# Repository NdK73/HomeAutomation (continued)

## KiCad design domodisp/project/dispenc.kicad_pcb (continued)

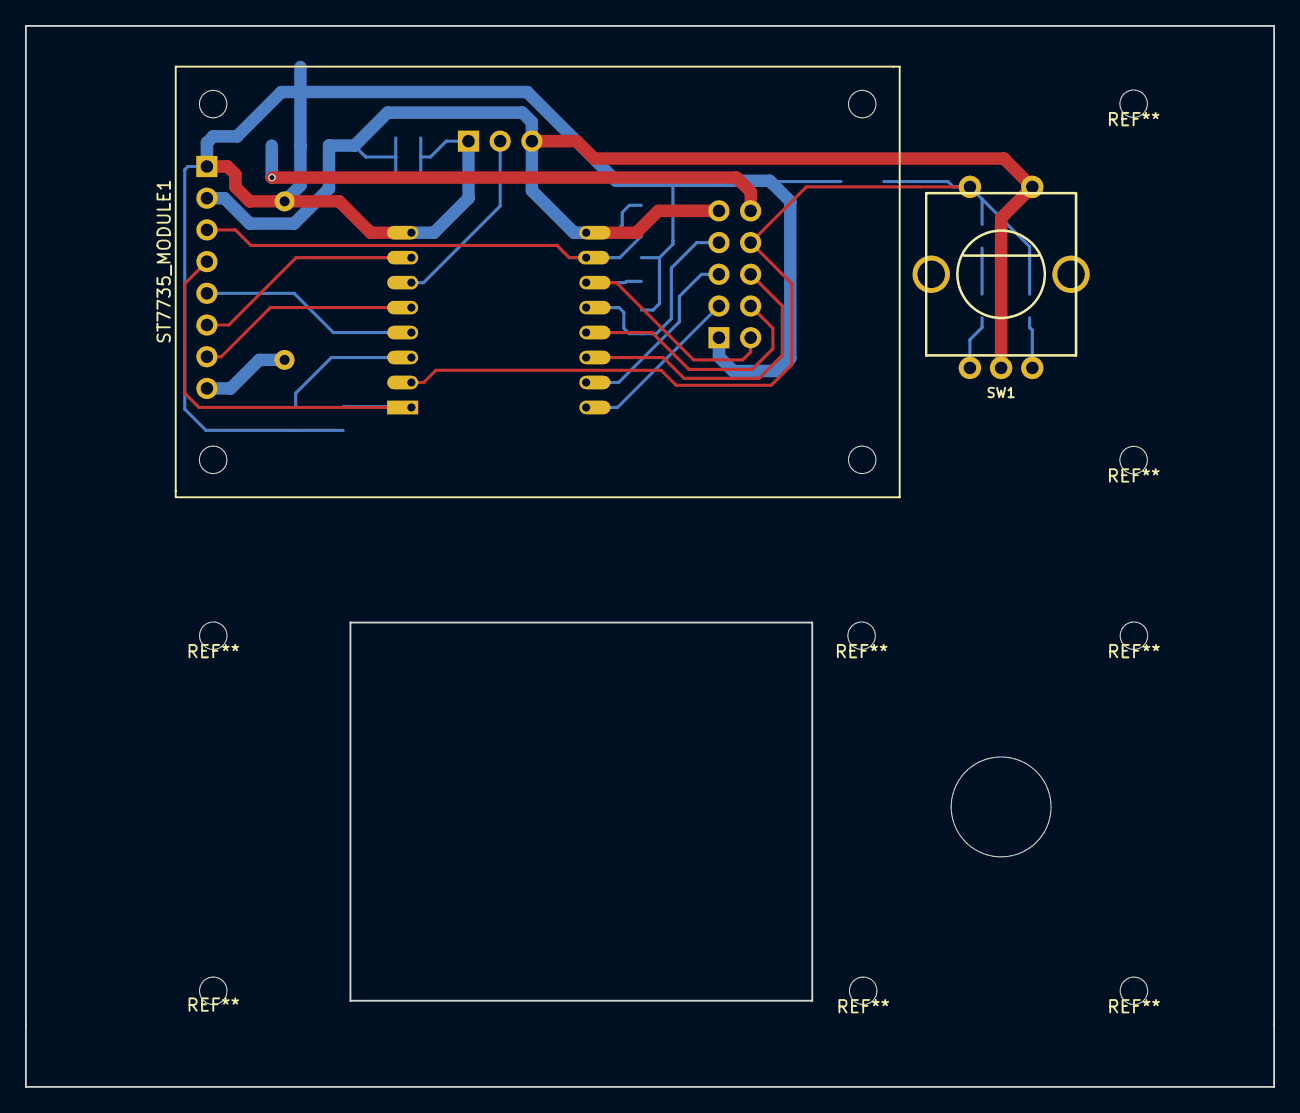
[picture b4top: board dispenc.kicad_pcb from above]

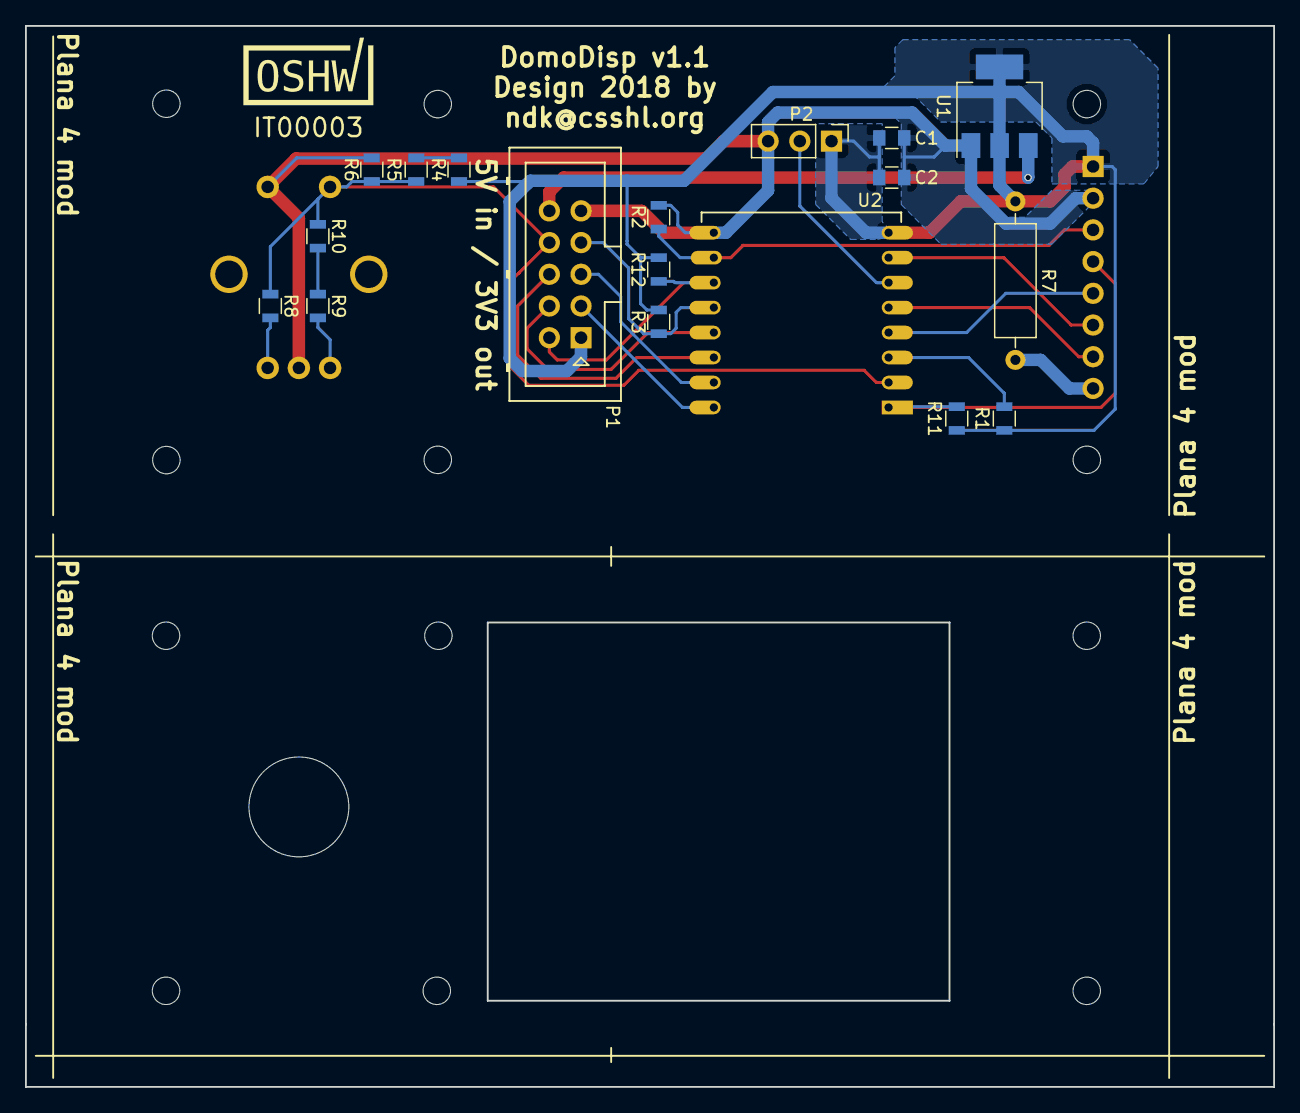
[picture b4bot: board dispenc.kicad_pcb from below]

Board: 2 copper layers, 100.0 x 85.0 mm, 21 parts (19 on the bottom side), 22 nets.

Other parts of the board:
OSHW_Mono_0.25_Scale: IT00003; OSHW_Mono_0.25_Scale
R12: 10k; R_0805

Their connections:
+3V3: R12.1; also elsewhere on the board
/DBG: R12.2; also elsewhere on the board

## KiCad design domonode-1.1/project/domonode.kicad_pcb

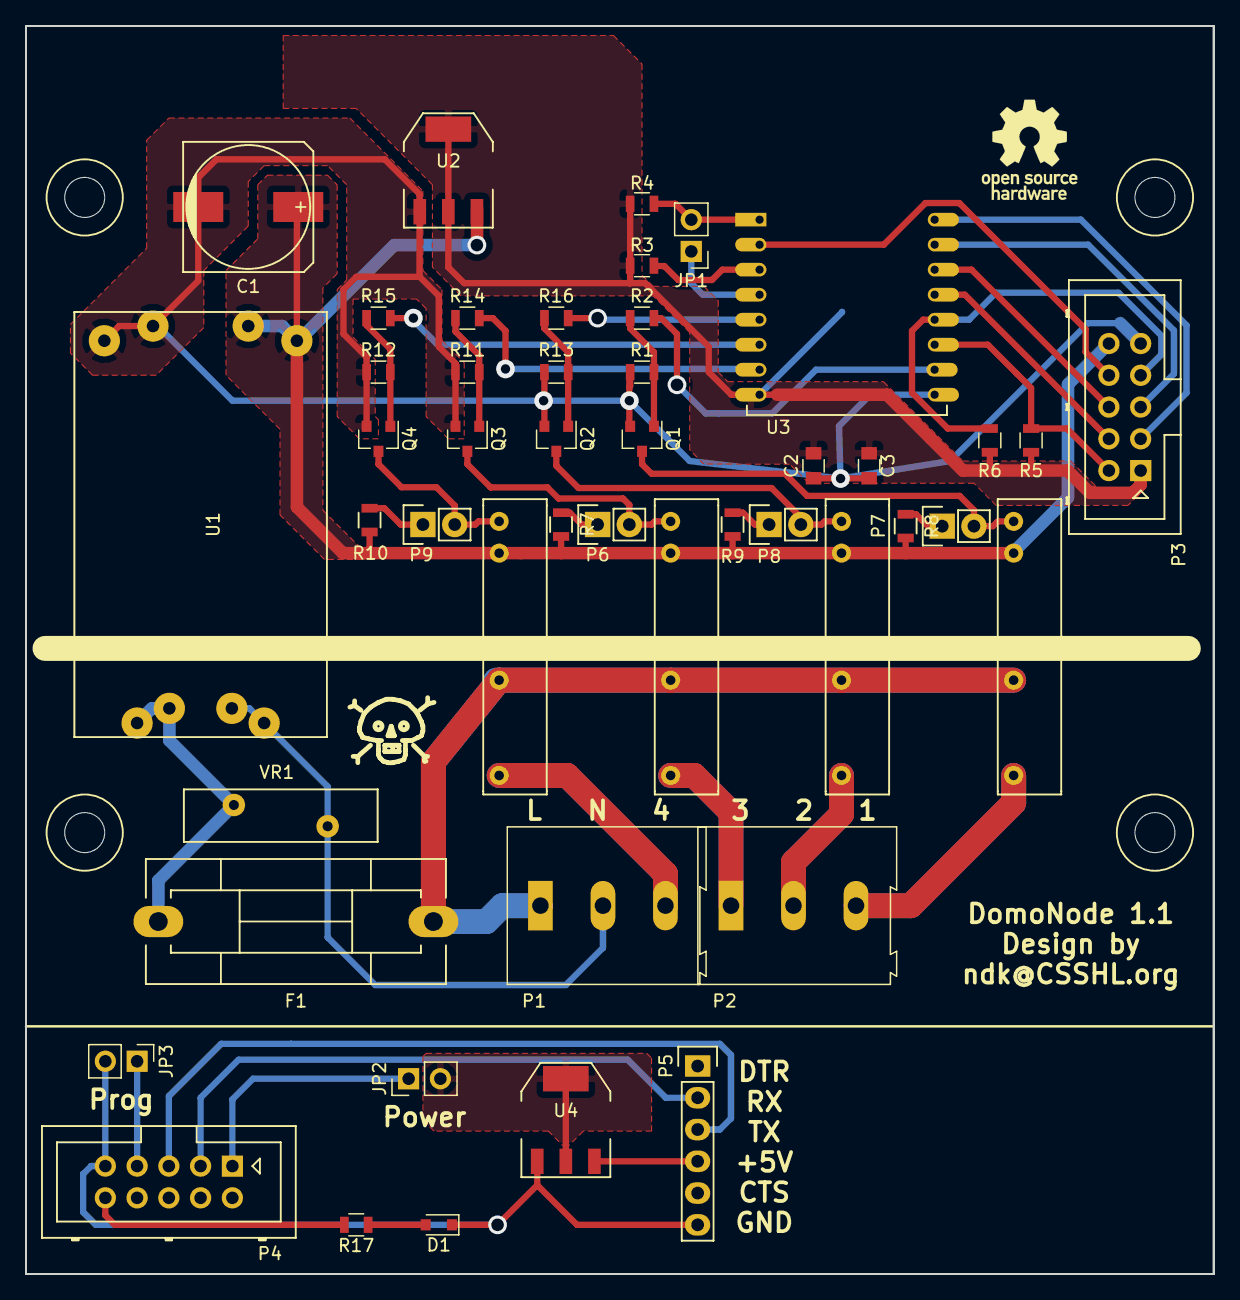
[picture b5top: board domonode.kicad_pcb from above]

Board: 2 copper layers, 95.0 x 99.8 mm, 48 parts (0 on the bottom side), 45 nets.

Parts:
BOX: Enclosure_DIN_6p_nomargin
C1: C; c_elec_10x10
C2: 10u; C_0805
C3: 100n; C_0805
D1: LED; D_0805
F1: FUSE; Fuseholder5x20_horiz_SemiClosed_Casing10x25mm
JP1: JUMPER; Pin_Header_Straight_1x02_Pitch2.54mm
JP2, JP3: Jumper; Pin_Header_Straight_1x02_Pitch2.54mm
P1, P2: CONN_01X03; AK300-3
P3, P4: CONN_2x5; Multicomp_MC9A12-1034_2x05x2.54mm_Straight
P5: CONN_01X06; Pin_Header_Straight_1x06
P6, P7, P8, P9: CONN_01X02; Pin_Header_Straight_1x02
Q1, Q2, Q3, Q4: 2n7002; SOT-23
R1, R3, R4, R5, R6, R11, R12, R13: 10k; R_0805
R2, R7, R8, R9, R10, R14, R15, R16, R17: 1k; R_0805
RL1, RL2, RL3, RL4: Omron_G3MB-202; G3MB
U1: HLK-PM01; ACDC-HLK+ND
U2, U4: AMS1117-3.3; SOT-223
U3: ESP-12
VR1: VR; RV_Disc_D15.5_W4.2_P7.5

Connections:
+3V3: C2.1, C3.1, P3.1, R3.1, R4.1, R5.1, R6.1, U2.2, U2.4, U3.8
+5V: C1.1, P3.10, R7.2, R8.2, R9.2, R10.2, RL1.3, RL2.3, RL3.3, RL4.3, U1.4, U2.3
/ADC: P3.8, U3.2
/DBG: P3.2, R5.2, U3.11
/L: F1.1, P1.1, RL1.2, RL2.2, RL3.2, RL4.2
/N: P1.2, U1.2, VR1.1
/PROG: P3.7, R6.2, U3.12
/P_GND: D1.1, JP3.2, P4.9, P5.6, U4.1
/P_PROG: JP3.1, P4.7
/P_RXD: P4.5, P5.3
/P_TXD: P4.3, P5.2
/RL1: R2.1, U3.10
/RL2: R16.1, U3.5
/RL3: R14.1, U3.7
/RL4: R15.1, U3.6
/RXD: P3.5, U3.15
/SCL: P3.4, U3.13
/SDA: P3.6, U3.14
/TXD: P3.3, U3.16
GND: C1.2, C2.2, C3.2, P3.9, Q1.2, Q2.2, Q3.2, Q4.2, R1.2, R11.2, R12.2, R13.2, U1.3, U2.1, U3.9
unnamed: D1.2, R17.1
unnamed: F1.2, U1.1, VR1.2
unnamed: JP1.1, U3.4
unnamed: JP1.2, R4.2, U3.1
unnamed: JP2.1, P4.1
unnamed: JP2.2, U4.2, U4.4
unnamed: P4.10, R17.2
unnamed: P5.4, U4.3
unnamed: P6.1, R7.1
unnamed: P6.2, Q3.3, RL3.4
unnamed: P7.1, R8.1
unnamed: P7.2, Q1.3, RL1.4
unnamed: P8.1, R9.1
unnamed: P8.2, Q2.3, RL2.4
unnamed: P9.1, R10.1
unnamed: P9.2, Q4.3, RL4.4
unnamed: Q1.1, R1.1, R2.2
unnamed: Q2.1, R13.1, R16.2
unnamed: Q3.1, R11.1, R14.2
unnamed: Q4.1, R12.1, R15.2
unnamed: R3.2, U3.3
RL1P: P2.3, RL1.1
RL2P: P2.2, RL2.1
RL3P: P2.1, RL3.1
RL4P: P1.3, RL4.1

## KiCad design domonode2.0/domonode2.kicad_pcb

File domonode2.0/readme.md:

## DomoNode 2.0

**Do not use:**. This folder is just for reference.

Evolution of DomoNode, but offers 6 inputs @ 230V, 6 SSR 2A@230V (each one have its own independent in and out lines, for maximum flexibility) and 8 independent LEDs, still in a 6-modules DIN rail enclosure. Kept SW compatibility with basic DomoNode (just the first 4 outputs), but different external connections.

Same expansion bus connector as the DomoNode 1.1.

I kept 2mm between L and N lines and it **ought** to be double-insulation, but it's actually not required: the user can't touch anything that is not already expected to be at 230V (screws in connectors) without opening the enclosure (the expansion connector **MUST NOT** be exposed).

The board requires two v-cuts around the central part, drawn on ECO2 layer (but not visible in the image). Once the two boards gets separated, the smaller one have to be mounted over the bigger one, using 2 **plastic** spacers (M3x15mm) and suitable 1x14 pins headers.

**Note**: Designed in KiCAD 5.1.5.

#### Known Problems

Fixed in v2.1:
 - **EPIC FAIL**: pulldowns instead of pullups on SDA and SCL :( -- it seems to work OK with internal ones, but could be a bit less stable
 - **FIXABLE FAIL**: SDA and SCL are reversed -- use Wire.begin(5,4);
 - Possible glitches at powerup on outputs: after a short power fail (~5s) MCP23017 outputs remain in the last state till setup() resets 'em (or indefinitely if you enter programming mode)
 - Trace for 3v3 to expansion connector is too thin
 - Traces from SSRs to Qn and from Qn to GND are too thin
 - Many traces are too long (to avoid vias)
 - You'll have to cut out about 2mm from the top of the break-out zone to allow the locks on the removable part of the connectors to engage

No need to fix in 2.1:
 - MCP23017 reset line goes to 3v3 instead of 5V

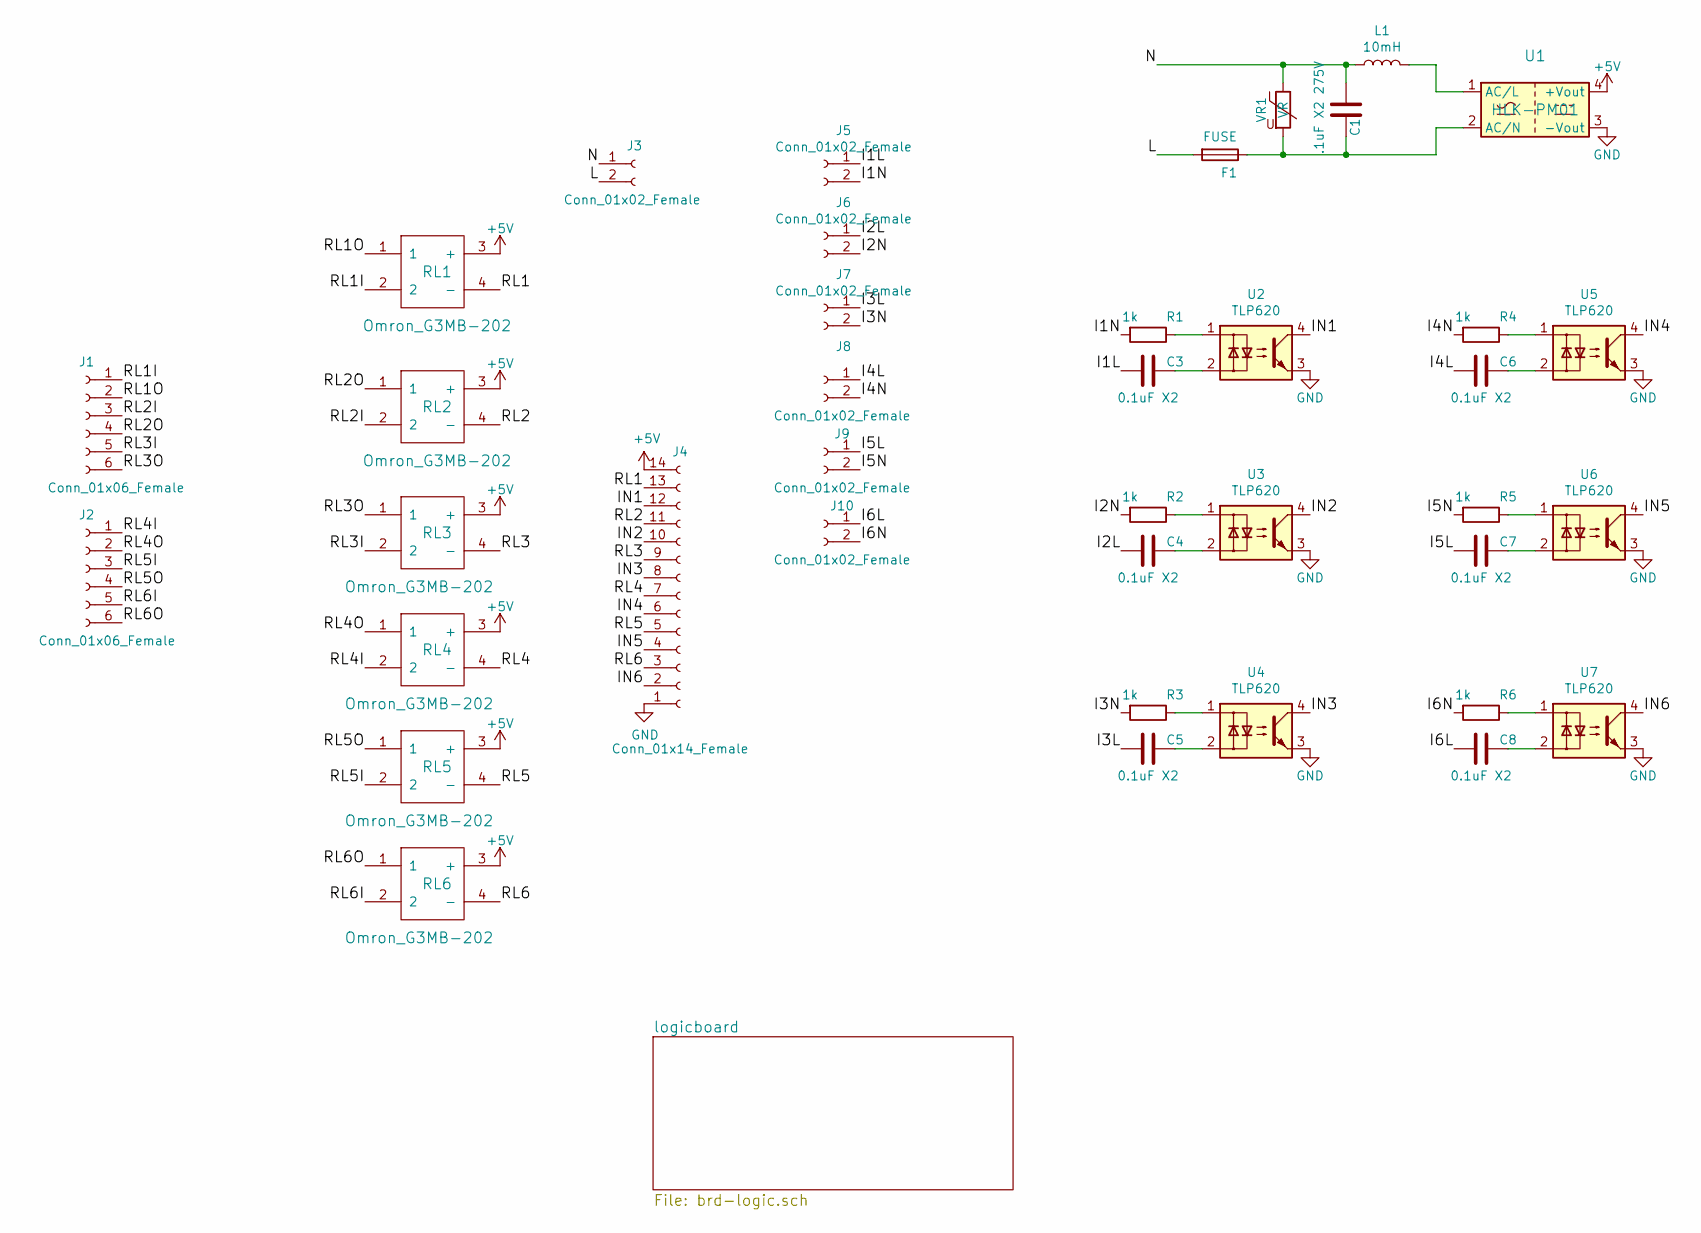
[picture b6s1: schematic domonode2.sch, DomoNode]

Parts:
C1: .1uF X2 275V; C_Rect_L13.0mm_W6.0mm_P10.00mm_FKS3_FKP3_MKS4
C3, C4, C5, C6, C7, C8: 0.1uF X2; C_Rect_L13.0mm_W6.0mm_P10.00mm_FKS3_FKP3_MKS4
F1: FUSE; Fuseholder5x20_horiz_SemiClosed_Casing10x25mm
J1, J2: Conn_01x06_Female; KF2EDGK-5.08-6
J3: Conn_01x02_Female; KF2EDGK-5.08-2
J4: Conn_01x14_Female; PinSocket_1x14_P2.54mm_Vertical
J5, J6, J7, J8, J9, J10: Conn_01x02_Female; KF2EDGK-3.81-2
L1: 10mH; INDUCTOR_0810
R1, R2, R3, R4, R5, R6: 1k; R_Axial_DIN0411_L9.9mm_D3.6mm_P12.70mm_Horizontal
RL1, RL2, RL3, RL4, RL5, RL6: Omron_G3MB-202; G3MB
U1: HLK-PM01; ACDC-HLK+ND
U2, U3, U4, U5, U6, U7: TLP620; DIP-4_W7.62mm_e_SOT-4
VR1: VR; RV_Disc_D15.5mm_W4.2mm_P7.5mm

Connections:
+5V: J4.14, RL1.3 (+), RL2.3 (+), RL3.3 (+), RL4.3 (+), RL5.3 (+), RL6.3 (+), U1.4 (+Vout)
/I1L: C3.2, J5.1
/I1N: J5.2, R1.2
/I2L: C4.2, J6.1
/I2N: J6.2, R2.2
/I3L: C5.2, J7.1
/I3N: J7.2, R3.2
/I4L: C6.2, J8.1
/I4N: J8.2, R4.2
/I5L: C7.2, J9.1
/I5N: J9.2, R5.2
/I6L: C8.2, J10.1
/I6N: J10.2, R6.2
/IN1: J4.12, U2.4
/IN2: J4.10, U3.4
/IN3: J4.8, U4.4
/IN4: J4.6, U5.4
/IN5: J4.4, U6.4
/IN6: J4.2, U7.4
/L: F1.2, J3.2
/N: C1.1, J3.1, L1.1, VR1.1
/RL1: J4.13, RL1.4 (-)
/RL1I: J1.1, RL1.2
/RL1O: J1.2, RL1.1
/RL2: J4.11, RL2.4 (-)
/RL2I: J1.3, RL2.2
/RL2O: J1.4, RL2.1
/RL3: J4.9, RL3.4 (-)
/RL3I: J1.5, RL3.2
/RL3O: J1.6, RL3.1
/RL4: J4.7, RL4.4 (-)
/RL4I: J2.1, RL4.2
/RL4O: J2.2, RL4.1
/RL5: J4.5, RL5.4 (-)
/RL5I: J2.3, RL5.2
/RL5O: J2.4, RL5.1
/RL6: J4.3, RL6.4 (-)
/RL6I: J2.5, RL6.2
/RL6O: J2.6, RL6.1
GND: J4.1, U1.3 (-Vout), U2.3, U3.3, U4.3, U5.3, U6.3, U7.3
unnamed: C1.2, F1.1, U1.2 (AC/N), VR1.2
unnamed: C3.1, U2.2
unnamed: C4.1, U3.2
unnamed: C5.1, U4.2
unnamed: C6.1, U5.2
unnamed: C7.1, U6.2
unnamed: C8.1, U7.2
unnamed: L1.2, U1.1 (AC/L)
unnamed: R1.1, U2.1
unnamed: R2.1, U3.1
unnamed: R3.1, U4.1
unnamed: R4.1, U5.1
unnamed: R5.1, U6.1
unnamed: R6.1, U7.1

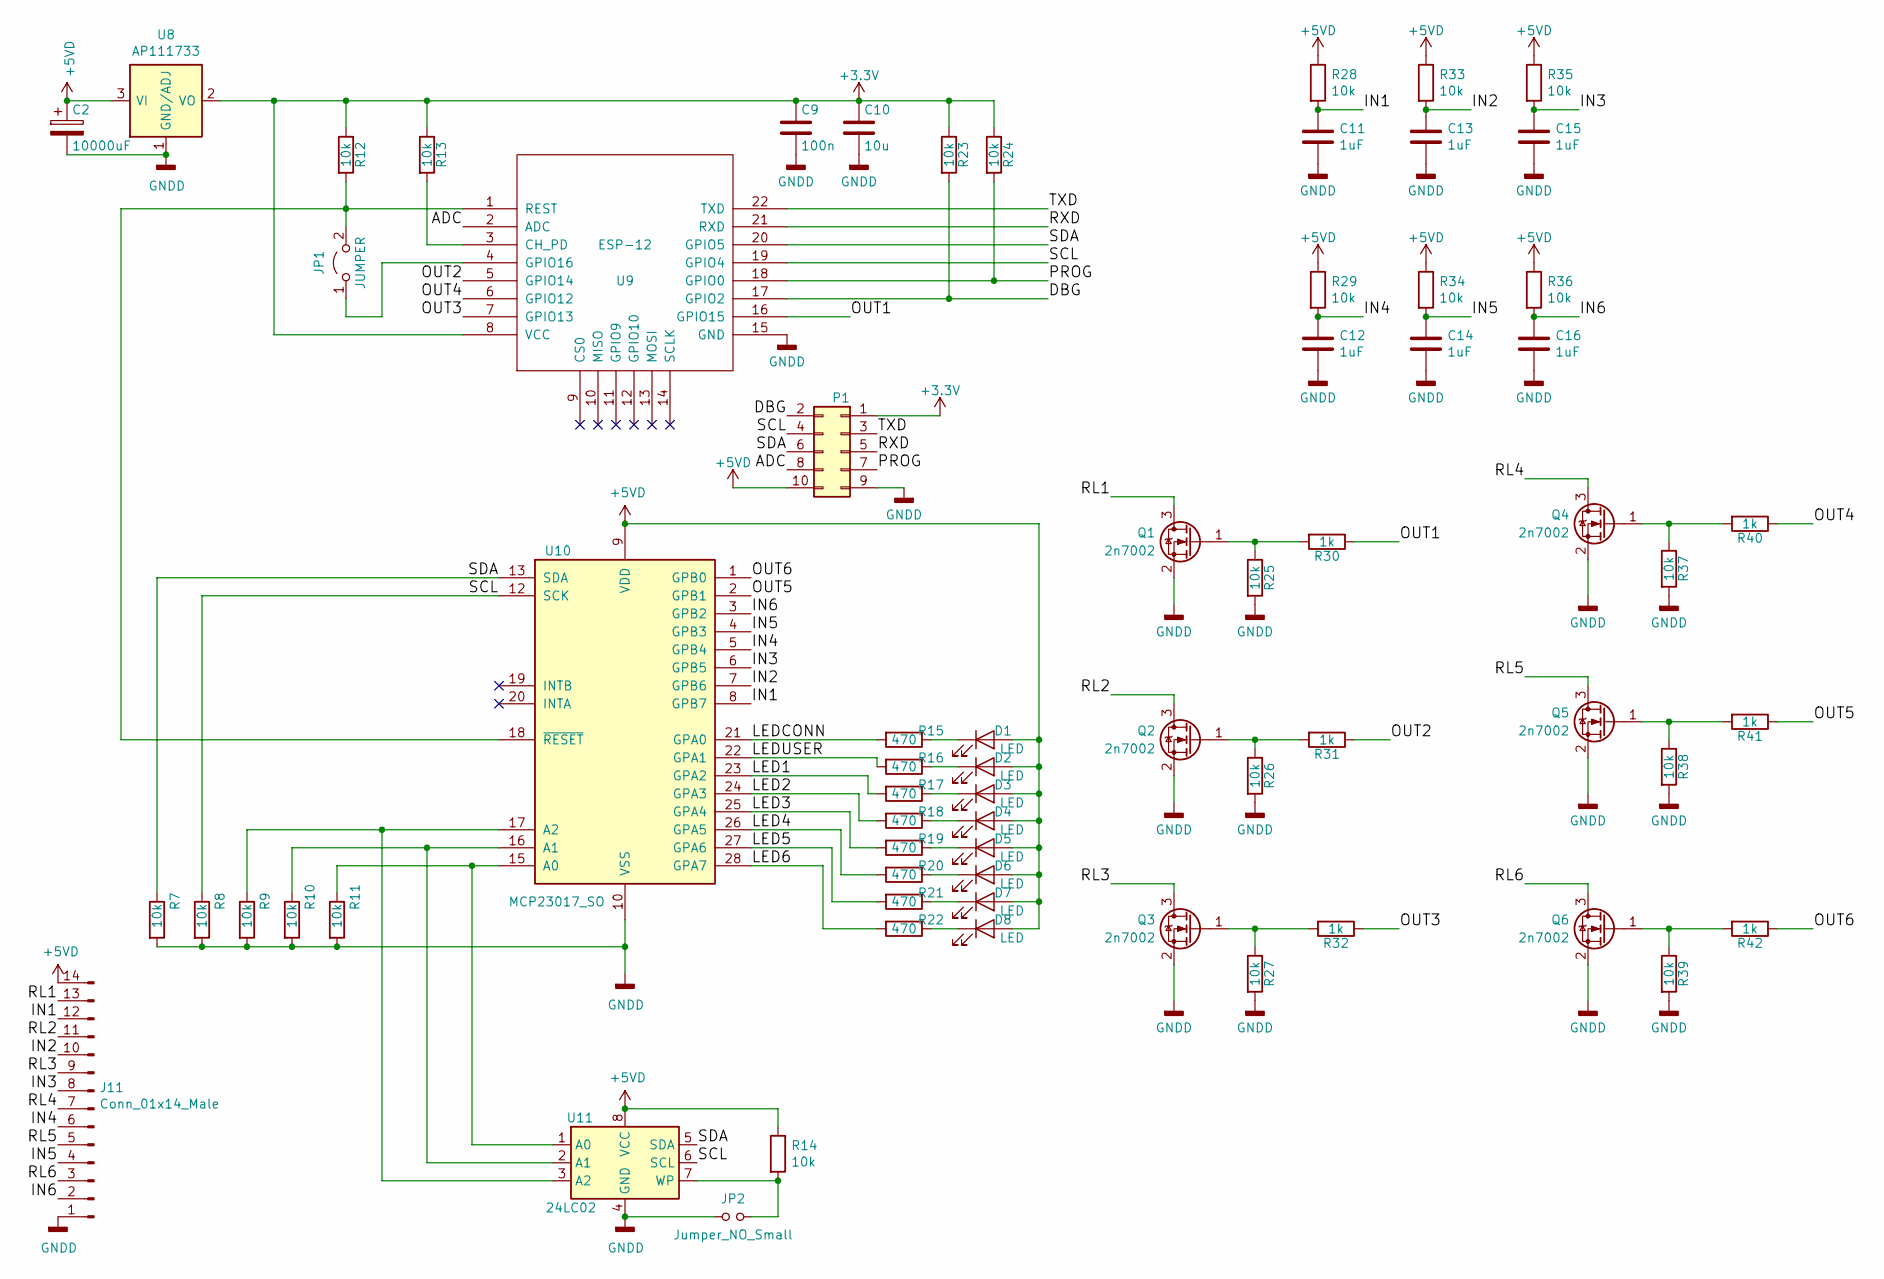
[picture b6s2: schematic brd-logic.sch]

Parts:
C2: 10000uF; CP_Elec_10x10
C9: 100n; C_0805_2012Metric
C10: 10u; C_0805_2012Metric
C11, C12, C13, C14, C15, C16: 1uF; C_0805_2012Metric
D1, D2, D3, D4, D5, D6, D7, D8: LED; LED_D3.0mm
J11: Conn_01x14_Male; PinSocket_1x14_P2.54mm_Vertical
JP1: JUMPER; PinSocket_1x02_P2.54mm_Vertical
JP2: Jumper_NO_Small; PinSocket_1x02_P2.54mm_Vertical
P1: CONN_2x5; Multicomp_MC9A12-1034_2x05_P2.54mm_Vertical
Q1, Q2, Q3, Q4, Q5, Q6: 2n7002; SOT-23
R7, R8, R9, R10, R11, R12, R13, R14, R23, R24, R25, R26, R27, R28, R29, R33, R34, R35, R36, R37, R38, R39: 10k; R_0805_2012Metric
R15, R16, R17, R18, R19, R20, R21, R22: 470; R_0805_2012Metric
R30, R31, R32, R40, R41, R42: 1k; R_0805_2012Metric
U8: AP111733; SOT-223-3_TabPin2
U9: ESP-12; ESP-12E
U10: MCP23017_SO; SOIC-28W_7.5x17.9mm_P1.27mm
U11: 24LC02; SOIC-8_3.9x4.9mm_P1.27mm

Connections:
+3V3: C9.1, C10.1, P1.1, R12.1, R13.1, R23.1, R24.1, U8.2 (VO), U9.8 (VCC)
+5VD: C2.1, D1.2 (A), D2.2 (A), D3.2 (A), D4.2 (A), D5.2 (A), D6.2 (A), D7.2 (A), D8.2 (A), J11.14, P1.10, R14.1, R28.1, R29.1, R33.1, R34.1, R35.1, R36.1, U8.3 (VI), U10.9 (VDD), U11.8 (VCC)
/logicboard/ADC: P1.8, U9.2 (ADC)
/logicboard/DBG: P1.2, R23.2, U9.17 (GPIO2)
/logicboard/IN1: C11.1, J11.12, R28.2, U10.8 (GPB7)
/logicboard/IN2: C13.1, J11.10, R33.2, U10.7 (GPB6)
/logicboard/IN3: C15.1, J11.8, R35.2, U10.6 (GPB5)
/logicboard/IN4: C12.1, J11.6, R29.2, U10.5 (GPB4)
/logicboard/IN5: C14.1, J11.4, R34.2, U10.4 (GPB3)
/logicboard/IN6: C16.1, J11.2, R36.2, U10.3 (GPB2)
/logicboard/LED1: R17.2, U10.23 (GPA2)
/logicboard/LED2: R18.2, U10.24 (GPA3)
/logicboard/LED3: R19.2, U10.25 (GPA4)
/logicboard/LED4: R20.2, U10.26 (GPA5)
/logicboard/LED5: R21.2, U10.27 (GPA6)
/logicboard/LED6: R22.2, U10.28 (GPA7)
/logicboard/LEDCONN: R15.2, U10.21 (GPA0)
/logicboard/LEDUSER: R16.2, U10.22 (GPA1)
/logicboard/OUT1: R30.1, U9.16 (GPIO15)
/logicboard/OUT2: R31.1, U9.5 (GPIO14)
/logicboard/OUT3: R32.1, U9.7 (GPIO13)
/logicboard/OUT4: R40.1, U9.6 (GPIO12)
/logicboard/OUT5: R41.1, U10.2 (GPB1)
/logicboard/OUT6: R42.1, U10.1 (GPB0)
/logicboard/PROG: P1.7, R24.2, U9.18 (GPIO0)
/logicboard/RL1: J11.13, Q1.3 (D)
/logicboard/RL2: J11.11, Q2.3 (D)
/logicboard/RL3: J11.9, Q3.3 (D)
/logicboard/RL4: J11.7, Q4.3 (D)
/logicboard/RL5: J11.5, Q5.3 (D)
/logicboard/RL6: J11.3, Q6.3 (D)
/logicboard/RXD: P1.5, U9.21 (RXD)
/logicboard/SCL: P1.4, R8.1, U9.19 (GPIO4), U10.12 (SCK), U11.6 (SCL)
/logicboard/SDA: P1.6, R7.1, U9.20 (GPIO5), U10.13 (SDA), U11.5 (SDA)
/logicboard/TXD: P1.3, U9.22 (TXD)
GNDD: C2.2, C9.2, C10.2, C11.2, C12.2, C13.2, C14.2, C15.2, C16.2, J11.1, JP2.1, P1.9, Q1.2 (S), Q2.2 (S), Q3.2 (S), Q4.2 (S), Q5.2 (S), Q6.2 (S), R7.2, R8.2, R9.2, R10.2, R11.2, R25.2, R26.2, R27.2, R37.2, R38.2, R39.2, U8.1 (GND/ADJ), U9.15 (GND), U10.10 (VSS), U11.4 (GND)
unnamed: D1.1 (K), R15.1
unnamed: D2.1 (K), R16.1
unnamed: D3.1 (K), R17.1
unnamed: D4.1 (K), R18.1
unnamed: D5.1 (K), R19.1
unnamed: D6.1 (K), R20.1
unnamed: D7.1 (K), R21.1
unnamed: D8.1 (K), R22.1
unnamed: JP1.1 (A), U9.4 (GPIO16)
unnamed: JP1.2 (B), R12.2, U9.1 (REST), U10.18 (~RESET~)
unnamed: JP2.2, R14.2, U11.7 (WP)
unnamed: Q1.1 (G), R25.1, R30.2
unnamed: Q2.1 (G), R26.1, R31.2
unnamed: Q3.1 (G), R27.1, R32.2
unnamed: Q4.1 (G), R37.1, R40.2
unnamed: Q5.1 (G), R38.1, R41.2
unnamed: Q6.1 (G), R39.1, R42.2
unnamed: R9.1, U10.17 (A2), U11.3 (A2)
unnamed: R10.1, U10.16 (A1), U11.2 (A1)
unnamed: R11.1, U10.15 (A0), U11.1 (A0)
unnamed: R13.2, U9.3 (CH_PD)

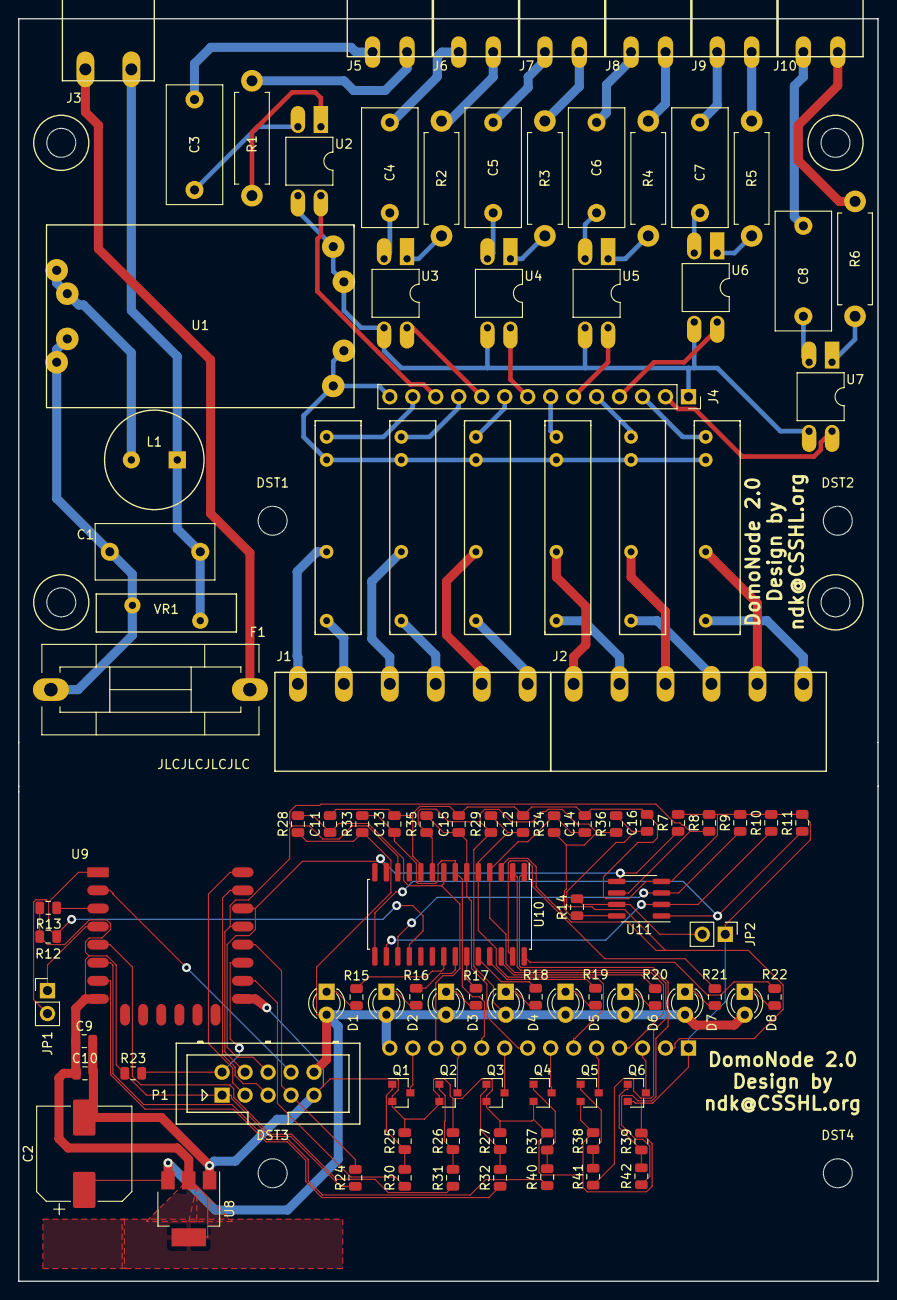
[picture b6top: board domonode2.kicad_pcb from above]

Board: 2 copper layers, 95.0 x 139.6 mm, 111 parts (1 on the bottom side), 111 nets.

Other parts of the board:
BOX: Enclosure_DIN_6p_nomargin
DST1, DST2, DST3, DST4: MountingHole_3.2mm_M3

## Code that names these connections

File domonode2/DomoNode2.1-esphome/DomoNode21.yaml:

esp8266:
  board: esp12e

i2c: # required for tca9555

tca9555:
  - id: exp0 # Consider only base IOs
    address: 0x20 # 20-27, 20 is the first expander, default would be 0x21

switch:
  - id: rl1
    name: "${upper_devicename} Relay 1"
    platform: gpio
    pin:
      number: GPIO15
  - id: rl2
    name: "${upper_devicename} Relay 2"
    platform: gpio
    pin:
      number: GPIO14
  - id: rl3
    name: "${upper_devicename} Relay 3"
    platform: gpio
    pin:
      number: GPIO13
  - id: rl4
    name: "${upper_devicename} Relay 4"
    platform: gpio
    pin:
      number: GPIO12
  - id: rl5
    name: "${upper_devicename} Relay 5"
    platform: gpio
    pin:
      tca9555: exp0
      number: 0
      mode: output
      #inverted: true
  - id: rl6
    name: "${upper_devicename} Relay 6"
    platform: gpio
    pin:
      tca9555: exp0
      number: 1
      mode: output
      #inverted: true

output:
  - id: pin_ledusr
    platform: gpio
    pin:
      tca9555: exp0
      number: 9
      mode: output
      #inverted: true
  - id: pin_led1
    platform: gpio
    pin:
      tca9555: exp0
      number: 10
      mode: output
      #inverted: true
  - id: pin_led2
    platform: gpio
    pin:
      tca9555: exp0
      number: 11
      mode: output
      #inverted: true
  - id: pin_led3
    platform: gpio
    pin:
      tca9555: exp0
      number: 12
      mode: output
      #inverted: true
  - id: pin_led4
    platform: gpio
    pin:
      tca9555: exp0
      number: 13
      mode: output
      #inverted: true
  - id: pin_led5
    platform: gpio
    pin:
      tca9555: exp0
      number: 14
      mode: output
      #inverted: true
  - id: pin_led6
    platform: gpio
    pin:
      tca9555: exp0
      number: 15
      mode: output
      #inverted: true

light:
  - id: ledconn
    platform: status_led
    #name: "${upper_devicename} Led Conn"
    #output: pin_ledconn
    pin:
      tca9555: exp0
      number: 8
      mode: output
      #inverted: true

  - id: ledusr
    platform: binary
    name: "${upper_devicename} Led Usr"
    output: pin_ledusr
    restore_mode: ALWAYS_OFF
  - id: led1
    platform: binary
    name: "${upper_devicename} Led 1"
    output: pin_led1
    restore_mode: ALWAYS_OFF
  - id: led2
    platform: binary
    name: "${upper_devicename} Led 2"
    output: pin_led2
    restore_mode: ALWAYS_OFF
  - id: led3
    name: "${upper_devicename} Led 3"
    platform: binary
    output: pin_led3
    restore_mode: ALWAYS_OFF
  - id: led4
    platform: binary
    name: "${upper_devicename} Led 4"
    output: pin_led4
    restore_mode: ALWAYS_OFF
  - id: led5
    platform: binary
    name: "${upper_devicename} Led 5"
    output: pin_led5
    restore_mode: ALWAYS_OFF
  - id: led6
    platform: binary
    name: "${upper_devicename} Led 6"
    output: pin_led6
    restore_mode: ALWAYS_OFF

binary_sensor:
  - id: in1
    name: "${upper_devicename} In 1"
    platform: gpio
    pin:
      tca9555: exp0
      number: 2
      mode: input
      #inverted: true
  - id: in2
    name: "${upper_devicename} In 2"
    platform: gpio
    pin:
      tca9555: exp0
      number: 3
      mode: input
      #inverted: true
  - id: in3
    name: "${upper_devicename} In 3"
    platform: gpio
    pin:
      tca9555: exp0
      number: 4
      mode: input
      #inverted: true
  - id: in4
    name: "${upper_devicename} In 4"
    platform: gpio
    pin:
      tca9555: exp0
      number: 5
      mode: input
      #inverted: true
  - id: in5
    name: "${upper_devicename} In 5"
    platform: gpio
    pin:
      tca9555: exp0
      number: 6
      mode: input
      #inverted: true
  - id: in6
    name: "${upper_devicename} In 6"
    platform: gpio
    pin:
      tca9555: exp0
      number: 7
      mode: input
      #inverted: true

wifi:
  ssid: !secret wifi_ssid
  password: !secret wifi_password
  fast_connect: true

  # Enable fallback hotspot (captive portal) in case wifi connection fails
  ap:
    ssid: "${upper_devicename}"
    password: !secret wifi_fallback_pass

captive_portal:

# Enable logging
logger:
  baud_rate: 0 # Do not log over serial port

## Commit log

2017-12-12 Initial (pre)release
2017-12-12 Added protocol documentation and design files
2017-12-13 Improved README.md
2017-12-13 Added license files
2017-12-13 Changed LICENSE to LICENSE.md to allow linking of other files
2017-12-13 Fixed wrong syntax for links
2017-12-15 R00: separated protocol version string from format and changed it to indicate WIP; removed commas between values (space is alreay a separator)
2017-12-18 DomoNode is now OSHWA-certified
2017-12-18 corrected link to OSHWA
2018-01-02 Added signed multicast packets spec; introduced cleaner notation for meaning of parameters
2018-01-02 Completed adoption of new notation in definitions; simplified explanation of TimeEvent
2018-01-02 Jan 2038 is for 'signed overflow', but we're using unsigned long
2018-01-02 Added timezone and dst info to TimeEvent packets
2018-01-03 Specified KiCAD version used
2018-01-04 Reorganized and expanded base docs; changed SignedUpdatePacket format
2018-01-04 Added warning about incompatible changes before 1.0.0
2018-01-07 Changed keyslot to keyID and changed R01 format
2018-01-07 Added example python code to generate time updates (slow)
2018-01-07 Changed dom-send.py to be able to send multicast packets
2018-01-07 Disabled forgotten debug messages in sendtime.py
2018-01-07 converted sig to hex (whoops!); added parsing of locale data for timezone and DST info
2018-01-08 reserved keyID 0000 for NULL method (DEBUG ONLY)
2018-01-08 DomoNode-inout is now certified OSHW
2018-01-08 Upgraded design of DomoNode-inout to 1.1.1; removed version from dir name
2018-01-08 Removed version from dir name for DomoNode
2018-01-08 Published current DomoDisp iteration (1.1)
2018-01-08 Linked TFT_eSPI lib and commented about reduced speed on breadboard
2018-01-08 Forgot to change keyID in sendtime.py -- now keyID 0000 is reserved
2018-01-09 DomoDisp is now certified by OSHWA (IT000003)
2018-01-09 Typo
2018-01-09 Fuzzyed KiCAD version
2018-01-10 keyid is no more part of the signature
2018-01-10 Do not consider time needed for signature verification: that must be addressed in the receiving node since different node types can have very different timings
2018-01-10 Added RegisterInfoSpec packet
2018-01-10 Fixed definition of SignedUpdatePkt and formalized AnswerPkt format
2018-01-10 Fixed InfoPacket definition to allow reading outputs status
2018-01-10 Changed (nonsense) RegisterInfoSpec to AnalogInfoSpec (IOs are only indirectly mapped to registers!)
2018-01-14 Small correction: note did not get updated when syntax changed
2018-01-14 Whitespace fix
2018-01-14 Changed AnalogInfoSpec toInfoSpec to be able to describe digital lines too
2018-01-15 add trailing newline on received answer
2018-01-26 Linked draft of protocol implementation
2018-03-25 Fixed a misunderstanding w/ Python time lib (see https://bugs.python.org/issue7229 )
2018-03-30 Added 'ClearSky technology' :-)
2018-05-08 Added placeholder entries for DomoInputs and DomoSwitch
2018-05-10 Added forgot design files for domonode-inout (1.1.1)
2018-05-10 Renamed domoinputs to domonode-inputs
2018-05-10 Added initial (untested) version of design files for domonode-inputs
2018-05-10 Corrected a typo
2018-05-10 Added preliminary notes about DomoDispV2
2018-05-11 Added some notes about HW
2018-05-11 Renamed domonode-inputs project files, replaced connectors, reduced isolation for 230V to 1.5mm (requires a PCB with solder mask)
2018-05-13 Updated DomoNode-Inout to 1.1.2 (improved connectors footprints)
2018-05-19 Reserved keyID FFFF
2018-05-24 Added error decoding to dom-send.py
2018-05-24 Added instructions for extensions, including memory map
2018-05-26 Minor edits (shortened lines, mostly)
2018-05-26 Added note to 16-bit read attempt
2018-05-27 Added note about setting HW config
2018-05-31 Reorganized DomoNode-Inputs files and added gerbers
2018-05-31 Added designs for DomoSwitch and panelized gerbers
2018-06-10 Update to v0.1.1 : use base64url (urlsafe charset, see RFC4648 table2) instead of base16 encoding for signatures
2018-06-12 Added missing bottom-soldermask in pads for 220V inputs
2018-06-16 Updated DomoNode-Inputs design files: - added component values in schematic (w/ minor changes for readability) - changed X2 capacitors footprint - moved filter capacitors to a regular pattern, where 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
2018-06-17 Changed EEPROM address-size detection algorithm and EEPROM layout
2018-06-21 Improved address-size detection algorithm description
2018-06-25 Updated protocol version in register description
2018-06-25 Reorganized registers descriptions -- should improve readability
2018-06-25 Every write to registers must be signed
2018-06-28 DomoNode-Inout: Fixed a really stupid error (swapped SCA/SCL on PCA9555); changed connector layout in schematic (from 1x10 to 2x5) for better readability
2019-09-14 Added warning about physical dimensions of DIN rail enclosure
2020-02-29 Initial DomoNode2.0 design files
2020-03-01 Various updates
2020-03-16 Added 'do not use' warning and 'known issues' section
2020-03-23 Linked article about certification of HLK-PM01
2020-03-31 Added 'errata' sections for DomoNode and DomoDisp
2020-03-31 Added more problems found in Domonode 2.0 (being fixed in 2.1)
2020-04-12 Added nistp256 key type to known types
2020-04-12 Extended hostname register, specified allowed characters and referenced RFC
2020-04-19 Slightly revised I2C memory address size detection algorithm
2020-05-24 Published DomoNode 2.1 design files and included docs about usable security chips
2020-05-30 Replaced code zipfile with actual files (to keep mods in git history)
2020-09-13 Added designs for DomoDisp enclosure for 504 wall box
2020-09-13 Fixed formatting typo
2020-09-13 Referenced the DomoDisp enclosure from the root readme
2021-11-08 Update README.md
    https://forum.kicad.info/t/warning-avoid-all-links-to-kicad-pcb-org-use-kicad-org/31521
2024-11-17 Added ESPHome template file for DomoNode 2.1
2024-11-17 Added errata for R15-R22 on DomoNode 2.1
2025-01-25 Update README.md
    Add note about inputs, EEPROM and crypto chip
